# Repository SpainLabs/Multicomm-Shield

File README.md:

Multicomm shield
================

Objetivo
________

Esta shield para Arduino se concibió en SpainLabs y está pensada para poder utilizar los módulos de comunicaciones más comunes de una forma sencilla.

Características
_______________

Los módulos serie que pueden acoplarse son el ESP8266 (ESP-01), HC05 y HC06, XBEE y además existen unos pines independientes para utilizar un dispositivo USB2UART por software.

Los módulos SPI que pueden acoplarse son el NRF24L01 y NRF905.

Al tener Arduino un sólo puerto serie, únicamente se puede utilizar un módulo de comunicaciones serie a la vez, en cambio los que usan el puerto spi pueden ser utilizados al mismo tiempo.

Además la shield incorpora dos formas de conexión para ampliar la lista de módulos:
- Aprovechando el zócalo para xbee, que puede ser activada o desactivada por un switch de 8 posiciones.
- Mediante un zócalo diseñado para placas de topos.

Lista de materiales
___________________

- **1 resistencia SMD 1206 de 10K** 0,01€ 
 http://es.aliexpress.com/item/-/1936731050.html
- **1 condensador SMD 1206 de 100nF** 0,01€
 http://es.aliexpress.com/item/Free-Shipping-100PCS-1206-104-100NF-0-1UF-1206-SMD-capacitance/1096160798.html
- **1 condensador SMD 1206 de 10UF** 0,02€
 http://es.aliexpress.com/item/QIAOTIAN-SMD-1206-Chip-Capacitor-10UF-106M-Y5V-10V-100PCS-Lot/1820137718.html
- **1 diodo SMT schottky** 0,02€
 http://es.aliexpress.com/item/Free-Shipping-100PCS-Schottky-Diode-1A-40V-1N5819-SS14-SMD-SMT/627622453.html
- **1 regulador SOT-223 ASM1117** 0,03€
 http://es.aliexpress.com/item/Free-Shipping-100PCS-Original-AMS1117-3-3-AMS1117-3-3V-AMS1117-1117-3-3V-1A-Voltage/1149210196.html
- **2 tiras de pines hembra de 2x4** 0,14€
 http://es.aliexpress.com/item/10x-2-54mm-2x4-Pins-Double-Row-Female-Straight-Header-Pitch-Socket-Pin-Strip-New/32243233137.html
- **1 tira de pines hembra de 2x7** 0,18€
 http://es.aliexpress.com/item/10PCS-2X7-Pin-14P-2-54mm-Double-Row-Female-Straight-Header-Pitch-Socket-Strip/1902481672.html
- **1 tira de pines hembra de 1x4** 0,07€
 http://es.aliexpress.com/item/40pcs-Golden-Single-Row-1x4-pins-2-54mm-Female-Header/877315473.html
- **2 tiras de pines hembra de 1x6** 0,08€
 http://es.aliexpress.com/item/-/2015371109.html
- **2 tiras de pines hembra de 1x10 2mm paso** 0,57€
 http://es.aliexpress.com/item/10-Pcs-Per-Lot-2mm-Pitch-10-Pin-Female-Single-Row-Straight-Pin-Header-Strip/32256838365.html
- **1 tira de pines macho de 1x40** 0,08€
 http://es.aliexpress.com/item/Free-Shipping-10pcs-40-Pin-1x40-Single-Row-Male-2-54-Breakable-Pin-Header-Connector-Strip/2035586129.html
- **1 switch dip de 8 posiciones** 0,19€
 http://www.ebay.co.uk/itm/50-pcs-DMR08T-Dip-Switch-SMD-8-Position-with-Tape-Seal-/261754060756

Librerías externas necesarias
_____________________________

Como la placa ha sido diseñada con el software CADSoft Eagle PCB Design, se han utilizado las siguientes librerías:

- Los diodos schottky de SparkFun-DiscreteSemi https://github.com/sparkfun/SparkFun-Eagle-Libraries
- La shield arduino y xbee de Adafruit https://github.com/adafruit/Adafruit-Eagle-Library

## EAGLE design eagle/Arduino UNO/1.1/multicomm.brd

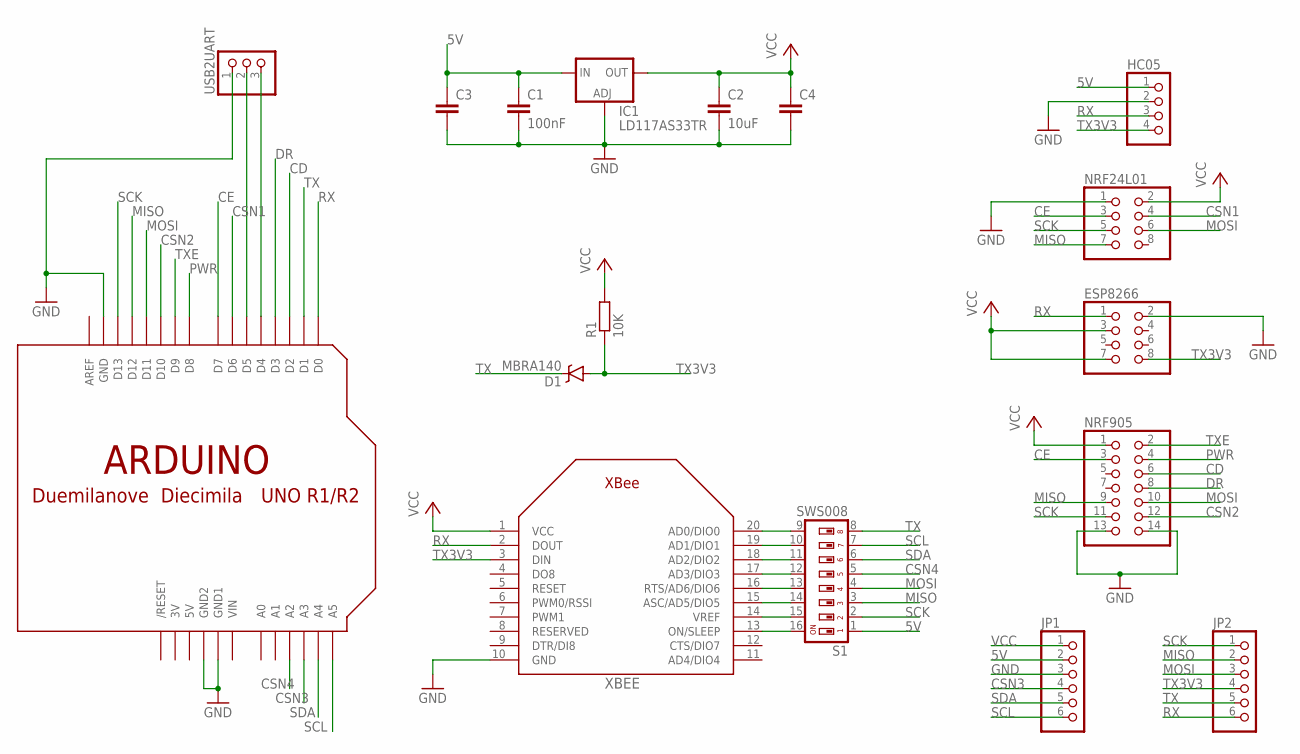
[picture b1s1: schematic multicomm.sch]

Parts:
C1: 100nF; C1206
C2: 10uF; C1206
C3, C4: C-EUC1206; C1206
D1: MBRA140; SMA-DIODE
ESP8266: PINHD-2X4; 2X04
HC05: PINHD-1X4; 1X04
IC1: LD117AS33TR; SOT223
JP1, JP2: PINHD-1X6; 1X06
NRF24L01: PINHD-2X4; 2X04
NRF905: PINHD-2X7; 2X07
R1: 10K; R1206
S1: SWS008; SMS-008
U$1: ARDUINO-NOHOLE
USB2UART: PINHD-1X3; 1X03
XBEE: XBEE

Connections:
3V: U$1.3V
5V: C1.1, C3.1, HC05.1, IC1.3 (IN), JP1.2, S1.1, U$1.5V
CD: NRF905.6, U$1.D2
CE: NRF24L01.3, NRF905.3, U$1.D7
CSN1: NRF24L01.4, U$1.D6
CSN2: NRF905.12, U$1.D10
CSN3: JP1.4, U$1.A3
CSN4: S1.5, U$1.A2
DR: NRF905.8, U$1.D3
GND: C1.2, C2.2, C3.2, C4.2, ESP8266.2, HC05.2, IC1.1 (ADJ), JP1.3, NRF24L01.1, NRF905.13, NRF905.14, U$1.GND, U$1.GND1, U$1.GND2, USB2UART.1, XBEE.10 (GND)
MISO: JP2.2, NRF24L01.7, NRF905.9, S1.3, U$1.D12
MOSI: JP2.3, NRF24L01.6, NRF905.10, S1.4, U$1.D11
unnamed: U$1.D4, USB2UART.3
unnamed: U$1.D5, USB2UART.2
unnamed: S1.9, XBEE.20 (AD0/DIO0)
unnamed: S1.10, XBEE.19 (AD1/DIO1)
unnamed: S1.11, XBEE.18 (AD2/DIO2)
unnamed: S1.12, XBEE.17 (AD3/DIO3)
unnamed: S1.13, XBEE.16 (RTS/AD6/DIO6)
unnamed: S1.14, XBEE.15 (ASC/AD5/DIO5)
unnamed: S1.15, XBEE.14 (VREF)
unnamed: S1.16, XBEE.13 (ON/SLEEP)
PWR: NRF905.4, U$1.D8
RX: ESP8266.1, HC05.3, JP2.6, U$1.D0, XBEE.2 (DOUT)
SCK: JP2.1, NRF24L01.5, NRF905.11, S1.2, U$1.D13
SCL: JP1.6, S1.7, U$1.A5
SDA: JP1.5, S1.6, U$1.A4
TX: D1.C, JP2.5, S1.8, U$1.D1
TX3V3: D1.A, ESP8266.8, HC05.4, JP2.4, R1.1, XBEE.3 (DIN)
TXE: NRF905.2, U$1.D9
VCC: C2.1, C4.1, ESP8266.3, ESP8266.7, IC1.4 (OUT), JP1.1, NRF24L01.2, NRF905.1, R1.2, XBEE.1 (VCC)
VIN: U$1.VIN

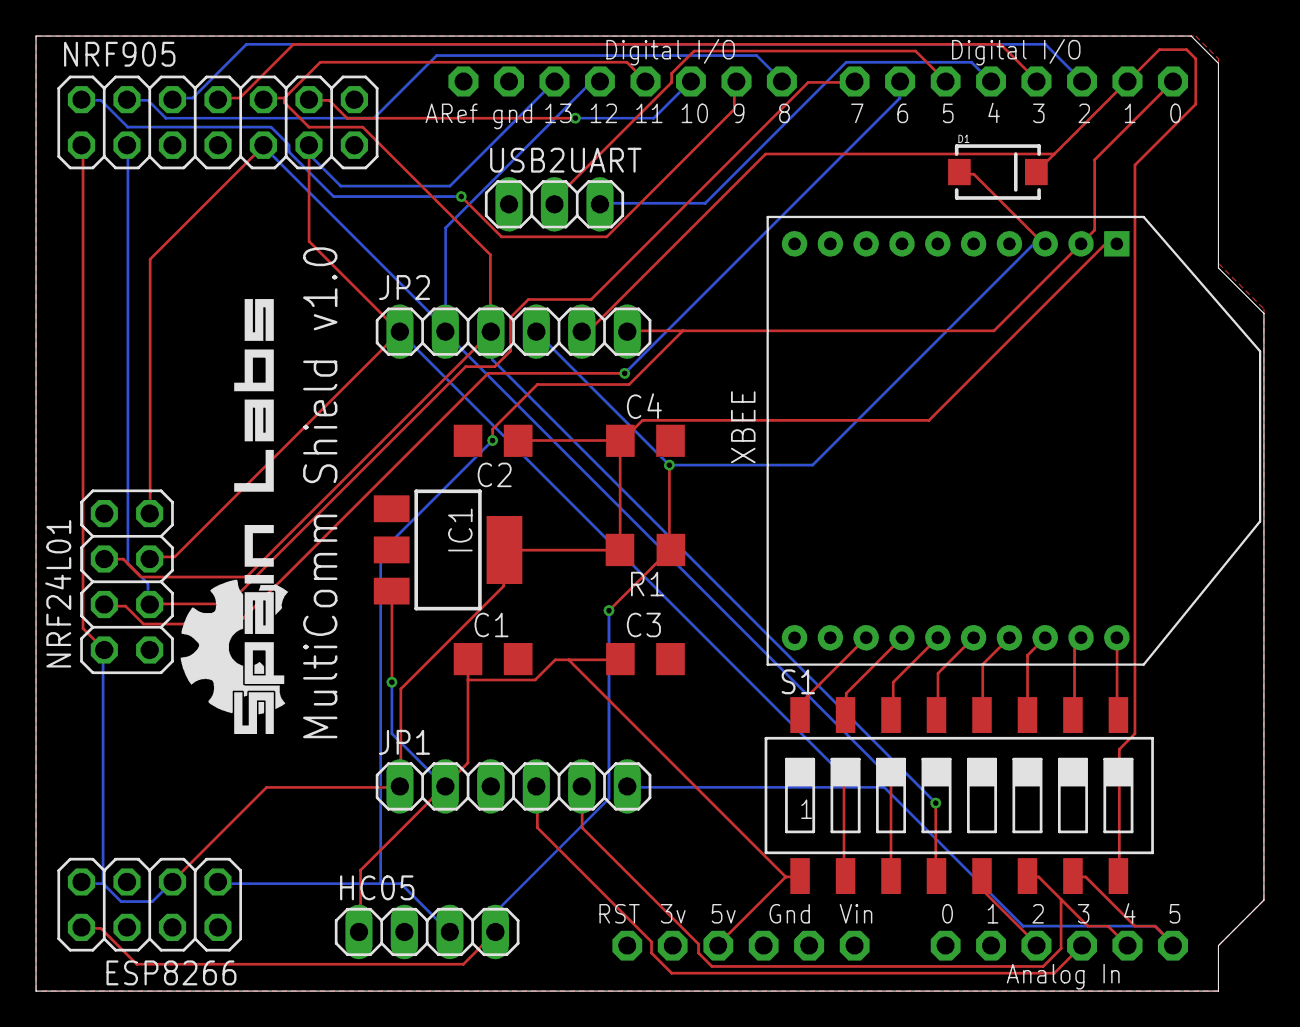
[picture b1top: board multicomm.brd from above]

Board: 2 copper layers, 68.6 x 53.3 mm, 18 parts (0 on the bottom side), 30 nets.

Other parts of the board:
U$2: SPAINLABS

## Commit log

2015-02-04 Create gh-pages branch via GitHub
2015-03-15 Ficheros de eagle
    Los ficheros del proyecto para el software de diseño de PCBs CadSoft
    Eagle. Este diseño está pensado para placas Arduino Diecimila,
    Duemilanove y UNO.
2015-03-15 Libreria de logos
    Contiene el logotipo de spainlabs para aplicarlo en la placa.
2015-03-16 Descripción del proyecto
2015-03-16 Información sobre la placa
2015-03-16 Descripción

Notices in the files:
parts and their libraries:
SparkFun-DiscreteSemi: Licensing: Creative Commons ShareAlike 4.0 International - https://creativecommons.org/licenses/by-sa/4.0
